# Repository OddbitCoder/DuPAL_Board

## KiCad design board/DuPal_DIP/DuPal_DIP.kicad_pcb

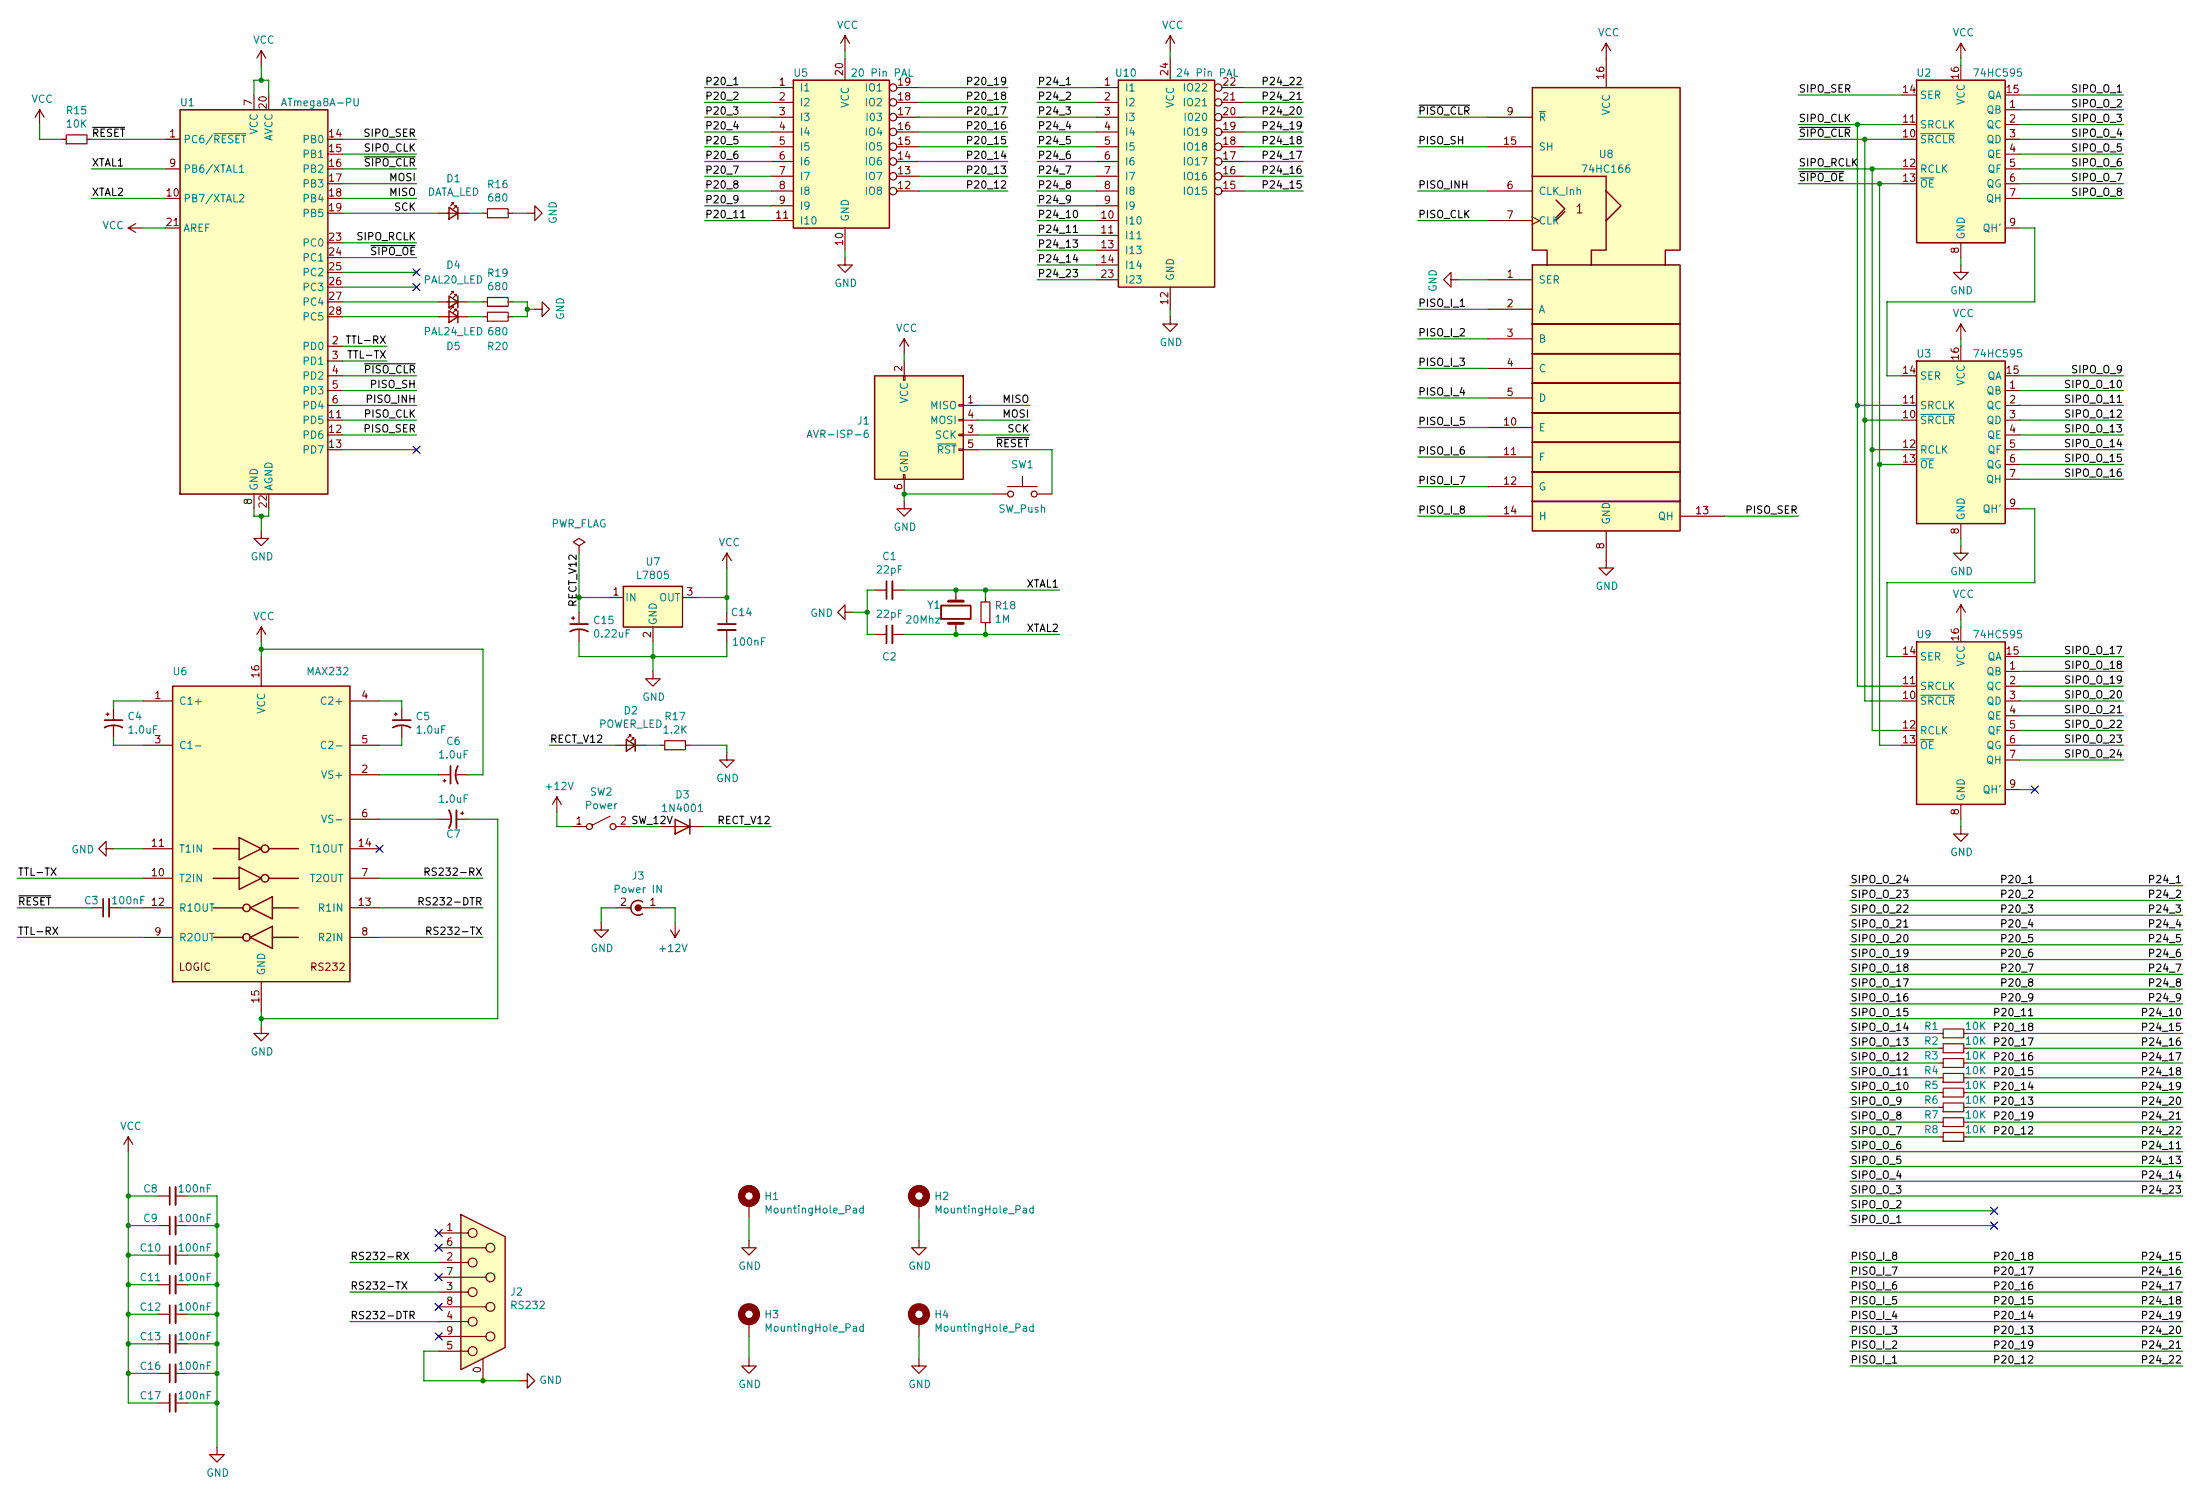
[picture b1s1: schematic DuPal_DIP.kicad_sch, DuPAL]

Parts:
C1, C2: 22pF; C_Disc_D3.0mm_W2.0mm_P2.50mm
C3, C8, C9, C10, C11, C12, C13, C14, C16, C17: 100nF; C_Disc_D3.4mm_W2.1mm_P2.50mm
C4, C5, C6, C7: 1.0uF; CP_Radial_D5.0mm_P2.50mm
C15: 0.22uF; CP_Radial_D5.0mm_P2.50mm
D1: DATA_LED; LED_D2.0mm_W4.8mm_H2.5mm_FlatTop
D2: POWER_LED; LED_D2.0mm_W4.8mm_H2.5mm_FlatTop
D3: 1N4001; D_DO-41_SOD81_P10.16mm_Horizontal
D4: PAL20_LED; LED_D2.0mm_W4.8mm_H2.5mm_FlatTop
D5: PAL24_LED; LED_D2.0mm_W4.8mm_H2.5mm_FlatTop
H1, H2, H3, H4: MountingHole_Pad; MountingHole_2.7mm_M2.5_ISO7380_Pad
J1: AVR-ISP-6; IDC-Header_2x03_P2.54mm_Vertical
J2: RS232; DSUB-9_Female_Horizontal_P2.77x2.84mm_EdgePinOffset4.94mm_H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
J3: Power IN; BarrelJack_Horizontal
R1, R2, R3, R4, R5, R6, R7, R8, R15: 10K; R_Axial_DIN0204_L3.6mm_D1.6mm_P7.62mm_Horizontal
R16, R19, R20: 680; R_Axial_DIN0204_L3.6mm_D1.6mm_P7.62mm_Horizontal
R17: 1.2K; R_Axial_DIN0204_L3.6mm_D1.6mm_P7.62mm_Horizontal
R18: 1M; R_Axial_DIN0204_L3.6mm_D1.6mm_P7.62mm_Horizontal
SW1: SW_Push; SW_PUSH_6mm
SW2: Power; SW_Slide_1P2T_CK_OS102011MS2Q
U1: ATmega8A-PU; DIP-28_W7.62mm
U2, U3, U9: 74HC595; DIP-16_W7.62mm
U5: 20 Pin PAL; DIP_Socket-20_W4.3_W5.08_W7.62_W10.16_W10.9_3M_220-3342-00-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
U6: MAX232; DIP-16_W7.62mm
U7: L7805; TO-220-3_Horizontal_TabDown
U8: 74HC166; DIP-16_W7.62mm
U10: 24 Pin PAL; DIP_Socket-24_W4.3_W5.08_W7.62_W10.16_W10.9_3M_224-5248-00-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
Y1: 20Mhz; Crystal_HC49-U_Vertical

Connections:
+12V: J3.1 (In), SW2.1 (A)
/MISO: J1.1 (MISO), U1.18 (PB4)
/MOSI: J1.4 (MOSI), U1.17 (PB3)
/P20_1: U5.1 (I1), U9.7 (QH), U10.1 (I1)
/P20_2: U5.2 (I2), U9.6 (QG), U10.2 (I2)
/P20_3: U5.3 (I3), U9.5 (QF), U10.3 (I3)
/P20_4: U5.4 (I4), U9.4 (QE), U10.4 (I4)
/P20_5: U5.5 (I5), U9.3 (QD), U10.5 (I5)
/P20_6: U5.6 (I6), U9.2 (QC), U10.6 (I6)
/P20_7: U5.7 (I7), U9.1 (QB), U10.7 (I7)
/P20_8: U5.8 (I8), U9.15 (QA), U10.8 (I8)
/P20_9: U3.7 (QH), U5.9 (I9), U10.9 (I9)
/P20_11: U3.6 (QG), U5.11 (I10), U10.10 (I10)
/P20_12: R8.2, U5.12 (IO8), U8.2 (A), U10.22 (IO22)
/P20_13: R6.2, U5.13 (IO7), U8.4 (C), U10.20 (I020)
/P20_14: R5.2, U5.14 (IO6), U8.5 (D), U10.19 (IO19)
/P20_15: R4.2, U5.15 (IO5), U8.10 (E), U10.18 (IO18)
/P20_16: R3.2, U5.16 (IO4), U8.11 (F), U10.17 (IO17)
/P20_17: R2.2, U5.17 (I03), U8.12 (G), U10.16 (IO16)
/P20_18: R1.2, U5.18 (IO2), U8.14 (H), U10.15 (IO15)
/P20_19: R7.2, U5.19 (IO1), U8.3 (B), U10.21 (IO21)
/P24_11: U2.5 (QF), U10.11 (I11)
/P24_13: U2.4 (QE), U10.13 (I13)
/P24_14: U2.3 (QD), U10.14 (I14)
/P24_23: U2.2 (QC), U10.23 (I23)
/PISO_CLK: U1.11 (PD5), U8.7 (CLK)
/PISO_INH: U1.6 (PD4), U8.6 (CLK_Inh)
/PISO_SER: U1.12 (PD6), U8.13 (QH)
/PISO_SH: U1.5 (PD3), U8.15 (SH)
/RECT_V12: C15.1, D2.2 (A), D3.1 (K), U7.1 (IN)
/RS232-DTR: J2.4, U6.13 (R1IN)
/RS232-RX: J2.2, U6.7 (T2OUT)
/RS232-TX: J2.3, U6.8 (R2IN)
/SCK: D1.2 (A), J1.3 (SCK), U1.19 (PB5)
/SIPO_CLK: U1.15 (PB1), U2.11 (SRCLK), U3.11 (SRCLK), U9.11 (SRCLK)
/SIPO_O_1: U2.15 (QA)
/SIPO_O_2: U2.1 (QB)
/SIPO_O_7: R8.1, U2.6 (QG)
/SIPO_O_8: R7.1, U2.7 (QH)
/SIPO_O_9: R6.1, U3.15 (QA)
/SIPO_O_10: R5.1, U3.1 (QB)
/SIPO_O_11: R4.1, U3.2 (QC)
/SIPO_O_12: R3.1, U3.3 (QD)
/SIPO_O_13: R2.1, U3.4 (QE)
/SIPO_O_14: R1.1, U3.5 (QF)
/SIPO_RCLK: U1.23 (PC0), U2.12 (RCLK), U3.12 (RCLK), U9.12 (RCLK)
/SIPO_SER: U1.14 (PB0), U2.14 (SER)
/SW_12V: D3.2 (A), SW2.2 (B)
/TTL-RX: U1.2 (PD0), U6.9 (R2OUT)
/TTL-TX: U1.3 (PD1), U6.10 (T2IN)
/XTAL1: C1.2, R18.2, U1.9 (PB6/XTAL1), Y1.2
/XTAL2: C2.2, R18.1, U1.10 (PB7/XTAL2), Y1.1
/~PISO_CLR: U1.4 (PD2), U8.9 (~R)
/~RESET: C3.1, J1.5 (~RST), R15.2, SW1.2, U1.1 (PC6/~RESET)
/~SIPO_CLR: U1.16 (PB2), U2.10 (~SRCLR), U3.10 (~SRCLR), U9.10 (~SRCLR)
/~SIPO_OE: U1.24 (PC1), U2.13 (~OE), U3.13 (~OE), U9.13 (~OE)
GND: C1.1, C2.1, C7.1, C8.2, C9.2, C10.2, C11.2, C12.2, C13.2, C14.2, C15.2, C16.2, C17.2, H1.1, H2.1, H3.1, H4.1, J1.6 (GND), J2.0 (PAD), J2.5, J3.2 (Ext), R16.2, R17.2, R19.2, R20.2, SW1.1, U1.8 (GND), U1.22 (AGND), U2.8 (GND), U3.8 (GND), U5.10 (GND), U6.11 (T1IN), U6.15 (GND), U7.2 (GND), U8.1 (SER), U8.8 (GND), U9.8 (GND), U10.12 (GND)
unnamed: D1.1 (K), R16.1
unnamed: D2.1 (K), R17.1
unnamed: D4.2 (A), U1.27 (PC4)
unnamed: D4.1 (K), R19.1
unnamed: D5.2 (A), U1.28 (PC5)
unnamed: D5.1 (K), R20.1
unnamed: U2.9 (QH'), U3.14 (SER)
unnamed: U3.9 (QH'), U9.14 (SER)
unnamed: C4.1, U6.1 (C1+)
unnamed: C4.2, U6.3 (C1-)
unnamed: C5.1, U6.4 (C2+)
unnamed: C5.2, U6.5 (C2-)
unnamed: C3.2, U6.12 (R1OUT)
unnamed: C6.1, U6.2 (VS+)
unnamed: C7.2, U6.6 (VS-)
VCC: C6.2, C8.1, C9.1, C10.1, C11.1, C12.1, C13.1, C14.1, C16.1, C17.1, J1.2 (VCC), R15.1, U1.7 (VCC), U1.20 (AVCC), U1.21 (AREF), U2.16 (VCC), U3.16 (VCC), U5.20 (VCC), U6.16 (VCC), U7.3 (OUT), U8.16 (VCC), U9.16 (VCC), U10.24 (VCC)

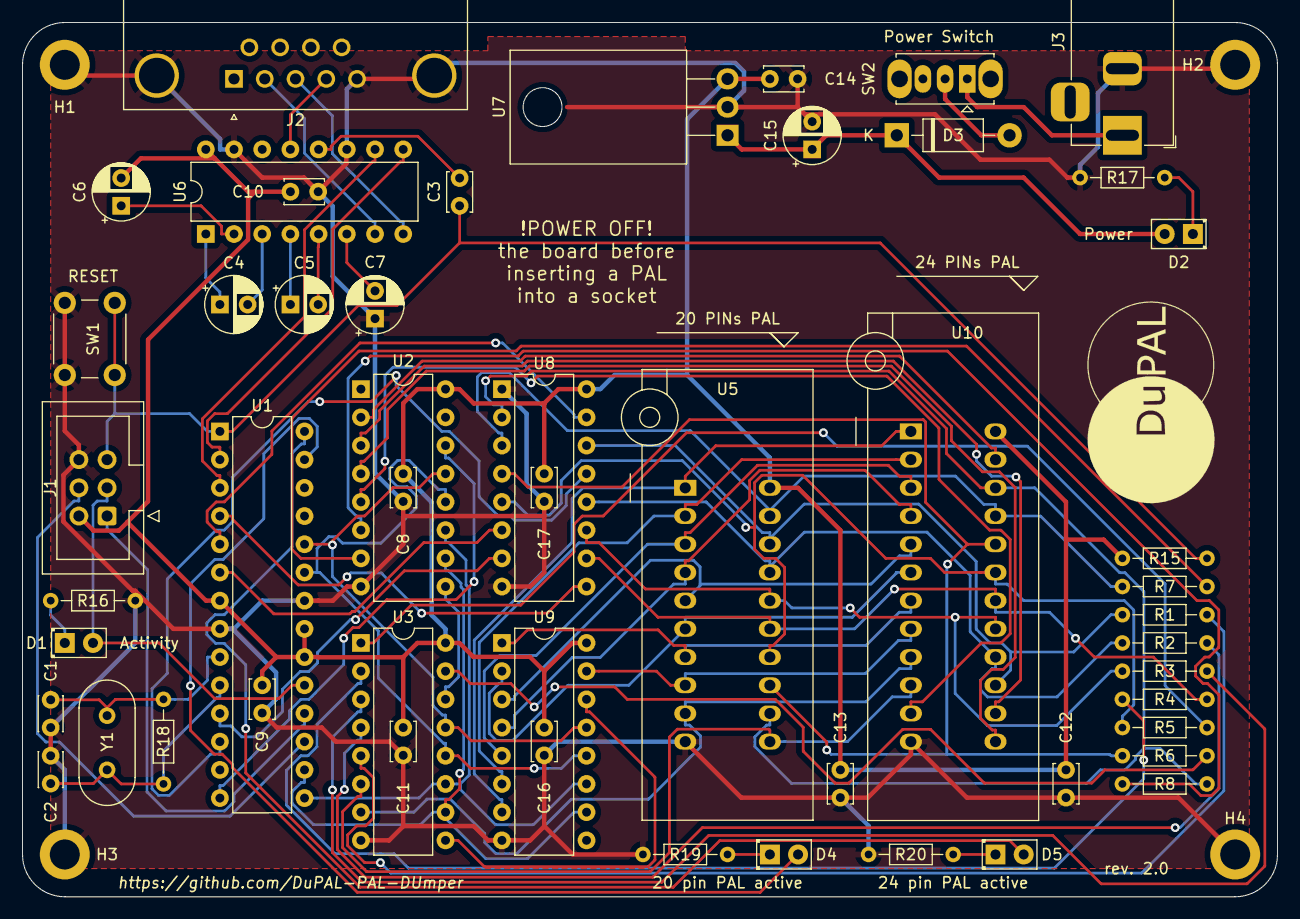
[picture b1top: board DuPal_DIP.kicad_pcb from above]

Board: 2 copper layers, 113.0 x 78.7 mm, 55 parts (0 on the bottom side), 71 nets.

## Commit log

2023-10-03 Adds new gerber files (sent to PCBWay)
2023-10-03 Updated to KiCad 7
2023-10-03 Updates to KiCad 7
2023-10-03 Fixes schematics
2023-10-04 Resolves ERC issues
2023-10-05 Resolves DRC issues
2023-10-13 Fixes crystal value
2023-10-13 Adds .gitignore (ignores backups and .lck files)
2023-10-24 Hides unconnected pins

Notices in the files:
board/DuPal_DIP/DuPal_DIP.kicad_pcb:
CC-BY-SA-4.0
